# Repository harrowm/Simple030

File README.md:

# Simple030
A simple 68030 SBC heavily based on the rosco_m68k 030 board and running that board's firmware.  

The idea is to run all the glue logic from a ATF1508 and to program the logic using verilog.  

Status of 11th Feb 2025, in design - not built or tested.  The verilog does program ok onto a ATF1508.

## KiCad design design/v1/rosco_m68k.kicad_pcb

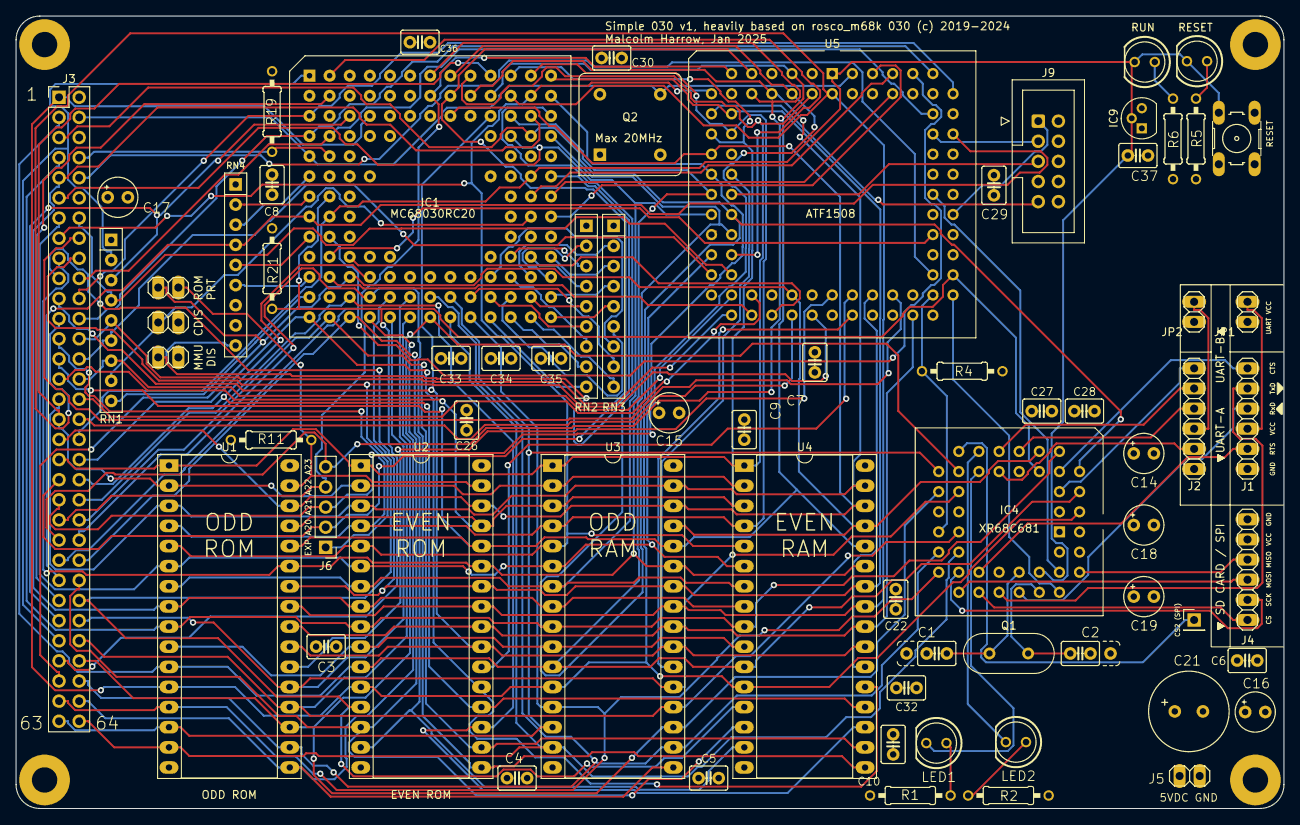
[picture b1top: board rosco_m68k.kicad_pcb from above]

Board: 4 copper layers, 160.0 x 100.0 mm, 73 parts (0 on the bottom side), 129 nets.

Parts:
C1, C2: 7pF; C2.5_or_3.5-3
C3, C4, C5, C6, C7, C8, C9, C10, C22, C26, C27, C28, C29, C30, C32, C33, C34, C35, C36: 100nF; C2.5-3
C14, C15, C16, C17, C18, C19: 100uF; E2,5-5
C21: 470uF; E3,5-10
C37: 0.01uF; C2.5-3
H1, H2, H3, H4: MountingHole; MountingHole_3.2mm_M3_Pad
IC1: MC68030RC_PGA; MC68030RC
IC4: XR68C681CJTR-F; PLCC-44_THT-Socket
IC9: DS1233-10+; TO-92
J1: UART_A; 1X06
J2: UART_B; 1X06
J3: Conn_02x32_Odd_Even; PinHeader_2x32_P2.54mm_Vertical
J4: Conn_01x06; 1X06
J5: PWR; 1X02
J6: Conn_01x05_Male; PinHeader_1x05_P2.54mm_Vertical
J7: Conn_01x01_Male; PinHeader_1x01_P2.54mm_Vertical
J9: Conn_02x05_Odd_Even; IDC-Header_2x05_P2.54mm_Vertical
JP1, JP2, JP3, JP5, JP6: Jumper; 1X02
LED1, LED6: GREEN; LED5MM
LED2, LED5: RED; LED5MM
Q1: 3.6864MHz; Crystal_HC49-4H_Vertical
Q2: 5H8ET-20.000; Oscillator_DIP-8
R1, R2: 330R; 0207_10
R4: 4K7; 0207_10
R5, R6: 1K; 0207_10
R11, R19: 10K; 0207_10
R21: 1K2; 0207_10
RN1, RN4: 4K7; R_Array_SIP9
RN2: 10K; R_Array_SIP9
RN3: R_Network08; R_Array_SIP9
SW1: SW_Push; B3F-10XX
U1, U2: SST39SF040; DIP-32_W15.24mm_Socket_LongPads
U3, U4: AS6C4008-55PCN; DIP-32_W15.24mm_Socket_LongPads
U5: ATF1508; PLCC-84_THT-Socket

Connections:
A0: IC1.A2 (A0), U5.29 (I/O)
A1: IC1.C4 (A1), IC4.2 (A1), J3.1, U1.12 (A0), U2.12 (A0), U3.12 (A0), U4.12 (A0), U5.28 (I/O)
A2: IC1.D13 (A2), IC4.4 (A2), J3.3, U1.11 (A1), U2.11 (A1), U3.11 (A1), U4.11 (A1), U5.27 (I/O)
A3: IC1.D12 (A3), IC4.6 (A3), J3.5, U1.10 (A2), U2.10 (A2), U3.10 (A2), U4.10 (A2), U5.25 (I/O)
A4: IC1.C13 (A4), IC4.7 (A4), J3.7, U1.9 (A3), U2.9 (A3), U3.9 (A3), U4.9 (A3)
A5: IC1.C12 (A5), J3.9, U1.8 (A4), U2.8 (A4), U3.8 (A4), U4.8 (A4)
A6: IC1.D11 (A6), J3.11, U1.7 (A5), U2.7 (A5), U3.7 (A5), U4.7 (A5), U5.24 (I/O)
A7: IC1.B13 (A7), J3.13, U1.6 (A6), U2.6 (A6), U3.6 (A6), U4.6 (A6), U5.20 (PD1/I/O)
A8: IC1.B12 (A8), J3.15, U1.5 (A7), U2.5 (A7), U3.5 (A7), U4.5 (A7), U5.12 (I/O)
A9: IC1.C11 (A9), J3.17, U1.27 (A8), U2.27 (A8), U3.27 (A8), U4.27 (A8), U5.22 (I/O)
A10: IC1.A13 (A10), J3.19, U1.26 (A9), U2.26 (A9), U3.26 (A9), U4.26 (A9), U5.15 (I/O)
A11: IC1.C10 (A11), J3.21, U1.23 (A10), U2.23 (A10), U3.23 (A10), U4.23 (A10), U5.21 (I/O)
A12: IC1.B11 (A12), J3.23, U1.25 (A11), U2.25 (A11), U3.25 (A11), U4.25 (A11), U5.2 (GCLK2/OE2/I)
A13: IC1.A12 (A13), J3.25, U1.4 (A12), U2.4 (A12), U3.4 (A12), U4.4 (A12), U5.17 (I/O)
A14: IC1.B10 (A14), J3.27, U1.28 (A13), U2.28 (A13), U3.28 (A13), U4.28 (A13), U5.5 (I/O)
A15: IC1.A11 (A15), J3.29, U1.29 (A14), U2.29 (A14), U3.3 (A14), U4.3 (A14), U5.16 (I/O)
A16: IC1.B9 (A16), J3.31, U1.3 (A15), U2.3 (A15), U3.31 (A15), U4.31 (A15), U5.8 (I/O)
A17: IC1.A10 (A17), J3.33, U1.2 (A16), U2.2 (A16), U3.2 (A16), U4.2 (A16)
A18: IC1.C8 (A18), J3.35, U1.30 (A17), U2.30 (A17), U3.30 (A17), U4.30 (A17), U5.18 (I/O)
A19: IC1.A9 (A19), J3.37, U1.1 (A18), U2.1 (A18), U3.1 (A18), U4.1 (A18), U5.4 (I/O)
A20: IC1.B8 (A20), J3.39, J6.2, U5.9 (I/O)
A21: IC1.A8 (A21), J3.41, J6.3, U5.6 (I/O)
A22: IC1.B7 (A22), J3.43, J6.4, U5.11 (I/O)
A23: IC1.A7 (A23), J3.45, J6.5, U5.10 (I/O)
AS: IC1.J2 (AS), J3.47, U5.77 (I/O)
BERR: IC1.H1 (BERR), J3.49, RN4.4 (R3), U5.70 (I/O)
BG: IC1.B2 (BG), J3.51
BGACK: IC1.C3 (BGACK), J3.53, RN1.3 (R2)
BR: IC1.A1 (BR), J3.55, RN1.2 (R1)
CBACK: IC1.J1 (CBACK), RN4.5 (R4)
CDIS: IC1.H12 (CDIS), JP6.1 (A), RN1.8 (R7)
CIIN: IC1.L1 (CIIN), RN4.6 (R5)
CLK: IC1.E1 (CLKIN), J3.4, Q2.5 (OUT), U5.83 (GCLK1/I)
CTSA: IC4.8 (IP0), J1.6
CTSB: IC4.5 (IP1), J2.6
D0: IC1.N9 (D16), IC4.28 (D0), J3.61, U1.13 (D0), U3.13 (DQ0)
D1: IC1.M8 (D17), IC4.18 (D1), J3.63, U1.14 (D1), U3.14 (DQ1)
D2: IC1.N8 (D18), IC4.27 (D2), J3.64, U1.15 (D2), U3.15 (DQ2)
D3: IC1.N7 (D19), IC4.19 (D3), J3.62, U1.17 (D3), U3.17 (DQ3)
D4: IC1.M7 (D20), IC4.26 (D4), J3.60, U1.18 (D4), U3.18 (DQ4)
D5: IC1.N6 (D21), IC4.20 (D5), J3.58, U1.19 (D5), U3.19 (DQ5)
D6: IC1.M6 (D22), IC4.25 (D6), J3.56, U1.20 (D6), U3.20 (DQ6)
D7: IC1.N5 (D23), IC4.21 (D7), J3.54, U1.21 (D7), U3.21 (DQ7)
D8: IC1.M5 (D24), J3.52, U2.13 (D0), U4.13 (DQ0)
D9: IC1.N4 (D25), J3.50, U2.14 (D1), U4.14 (DQ1)
D10: IC1.N3 (D26), J3.48, U2.15 (D2), U4.15 (DQ2)
D11: IC1.M4 (D27), J3.46, U2.17 (D3), U4.17 (DQ3)
D12: IC1.N2 (D28), J3.44, U2.18 (D4), U4.18 (DQ4)
D13: IC1.M3 (D29), J3.42, U2.19 (D5), U4.19 (DQ5)
D14: IC1.L4 (D30), J3.40, U2.20 (D6), U4.20 (DQ6)
D15: IC1.N1 (D31), J3.38, U2.21 (D7), U4.21 (DQ7)
DBEN: IC1.M1 (DBEN), RN1.9 (R8)
DS: IC1.K2 (DS), U5.61 (I/O)
DSACK0: IC1.F1 (DSACK0), RN4.3 (R2)
DTACK: IC1.G2 (DSACK1), IC4.10 (*DTALK), J3.57, R21.2, U5.56 (I/O)
DUAIACK: IC4.41 (*IACK), U5.65 (I/O)
DUAIRQ: IC4.24 (INTR), R4.2, U5.55 (I/O)
DUASEL: IC4.39 (CS), U5.54 (I/O)
E: J3.10, U5.57 (I/O)
EVENRAMSEL: U4.22 (CE), U5.48 (I/O)
EVENROMSEL: U2.22 (CE), U5.46 (I/O/PD2)
EXPSEL: J3.18, J6.1, U5.41 (I/O)
FC0: IC1.D2 (FC0), J3.20, U5.73 (I/O)
FC1: IC1.C1 (FC1), J3.22, U5.74 (I/O)
FC2: IC1.D1 (FC2), J3.24, U5.75 (I/O)
GND: C1.1, C2.1, C3.2, C4.2, C5.2, C6.2, C7.2, C8.2, C9.2, C10.2, C14.-, C15.-, C16.-, C17.-, C18.-, C19.-, C21.-, C22.2, C26.2, C27.2, C28.1, C29.1, C30.1, C32.2, C33.2, C34.2, C35.2, C36.2, C37.2, H1.1, H2.1, H3.1, H4.1, IC1.C5 (GND), IC1.C7 (GND), IC1.C9 (GND), IC1.E3 (GND), IC1.E11 (GND), IC1.F3 (GND), IC1.G3 (GND), IC1.G11 (GND), IC1.J3 (GND), IC1.J11 (GND), IC1.L5 (GND), IC1.L7 (GND), IC1.L8 (GND), IC1.L9 (GND), IC4.3 (IP3), IC4.22 (GND), IC4.42 (IP5), IC4.43 (IP4), IC9.1 (GND), J1.1, J2.1, J3.6, J4.6, J5.2, J9.2, J9.10, JP5.2 (B), JP6.2 (B), Q2.4 (GND), R6.2, RN2.1 (common), RN3.1 (common), SW1.1, U1.16 (GND), U2.16 (GND), U3.16 (VSS), U4.16 (VSS), U5.7 (GND), U5.19 (GND), U5.32 (GND), U5.42 (GND), U5.47 (GND), U5.59 (GND), U5.72 (GND), U5.82 (GND)
HALT: C37.1, IC1.F12 (RESET), IC1.H2 (HLT), IC4.38 (*RESET), IC9.2 (~RST), J3.36, LED5.K (C), LED6.K (C), SW1.2, U5.1 (GCLR/I)
IOSEL: J3.16, U5.50 (I/O)
IPL0: IC1.H13 (IPL0), U5.81 (GCLK3/I/O)
IPL1: IC1.G13 (IPL1), U5.80 (I/O)
IPL2: IC1.G12 (IPL2), U5.79 (I/O)
IRQ2: J3.28, RN1.6 (R5), U5.30 (I/O)
IRQ3: J3.14, RN1.4 (R3), U5.31 (I/O)
IRQ5: J3.26, RN1.5 (R4), U5.33 (I/O)
IRQ6: J3.30, RN1.7 (R6), U5.34 (I/O)
LDS: J3.32, U5.36 (I/O)
MMUDIS: IC1.F13 (MMUDIS), JP5.1 (A), RN4.9 (R8)
unnamed: IC4.15 (OP3), LED2.K (C)
unnamed: IC4.16 (OP5), LED1.K (C)
unnamed: C1.2, IC4.36 (X1/CLK), Q1.1
unnamed: C2.2, IC4.37 (X2), Q1.2
unnamed: LED1.A, R1.1
unnamed: LED2.A, R2.1
unnamed: LED5.A, R5.1
unnamed: LED6.A, R6.1
ODDRAMSEL: U3.22 (CE), U5.45 (I/O)
ODDROMSEL: U1.22 (CE), U5.44 (I/O)
ROM_RW: JP3.2 (B), R11.2, U1.31 (PGM), U2.31 (PGM)
RTSA: IC4.32 (OP0), J1.2
RTSB: IC4.14 (OP1), J2.2
RW: IC1.L3 (R_W), IC4.9 (*R/*W), J3.59, JP3.1 (A), U3.29 (WE), U4.29 (WE), U5.40 (I/O)
RXDA: IC4.35 (RXDA), J1.4
RXDB: IC4.11 (RXDB), J2.4
SIZ0: IC1.L2 (SIZ0), U5.35 (I/O)
SIZ1: IC1.K3 (SIZ1), U5.37 (I/O)
SPICLK: IC4.30 (OP4), J4.2
SPICS: IC4.31 (OP2), J4.1
SPICS2: IC4.17 (OP7), J7.1
SPIMISO: IC4.40 (IP2), J4.4
SPIMOSI: IC4.29 (OP6), J4.3
STERM: IC1.G1 (STERM), RN4.2 (R1)
TCK: J9.1, U5.62 (TCK/I/O)
TDI: J9.9, U5.14 (TDI/I/O)
TDO: J9.3, U5.71 (TDO/I/O)
TMS: J9.5, U5.23 (TMS/I/O)
TXDA: IC4.33 (TXDA), J1.5
TXDB: IC4.13 (TXDB), J2.5
UD0: IC1.K13 (D0), RN3.3 (R2)
UD1: IC1.K12 (D1), RN2.4 (R3)
UD2: IC1.L13 (D2), RN2.2 (R1)
UD3: IC1.M13 (D3), RN3.4 (R3)
UD4: IC1.L12 (D4), RN3.2 (R1)
UD5: IC1.K11 (D5), RN2.3 (R2)
UD6: IC1.M12 (D6), RN2.5 (R4)
UD7: IC1.L11 (D7), RN2.7 (R6)
UD8: IC1.N13 (D8), RN3.5 (R4)
UD9: IC1.M11 (D9), RN3.6 (R5)
UD10: IC1.L10 (D10), RN3.7 (R6)
UD11: IC1.N12 (D11), RN3.9 (R8)
UD12: IC1.M10 (D12), RN2.6 (R5)
UD13: IC1.N11 (D13), RN2.8 (R7)
UD14: IC1.M9 (D14), RN3.8 (R7)
UD15: IC1.N10 (D15), RN2.9 (R8)
UDS: J3.34, U5.39 (I/O)
VCC: C3.1, C4.1, C5.1, C6.1, C7.1, C8.1, C9.1, C10.1, C14.+, C15.+, C16.+, C17.+, C18.+, C19.+, C21.+, C22.1, C26.1, C27.1, C28.2, C29.2, C30.2, C32.1, C33.1, C34.1, C35.1, C36.1, IC1.C6 (VCC), IC1.D4 (VCC), IC1.D10 (VCC), IC1.F2 (VCC), IC1.F11 (VCC), IC1.H3 (VCC), IC1.H11 (VCC), IC1.K4 (VCC), IC1.K10 (VCC), IC1.L6 (VCC), IC4.44 (VCC), IC9.3 (VCC), J3.2, J4.5, J5.1, JP1.2 (B), JP2.2 (B), Q2.8 (Vcc), R1.2, R2.2, R4.1, R5.2, R11.1, R19.1, R21.1, RN1.1 (common), RN4.1 (common), U1.32 (VCC), U2.32 (VCC), U3.32 (VCC), U4.32 (VCC), U5.3 (VCCINT), U5.13 (VCCIO), U5.26 (VCCIO), U5.38 (VCCIO), U5.43 (VCCINT), U5.53 (VCCIO), U5.66 (VCCIO), U5.78 (VCCIO)
VCCUA: J1.3, JP1.1 (A)
VCCUB: J2.3, JP2.1 (A)
VPA: IC1.E2 (AVEC), J3.8, R19.2
WR: U1.24 (OE), U2.24 (OE), U3.24 (OE), U4.24 (OE), U5.51 (I/O)

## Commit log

2025-01-27 Tidy of files
2025-01-27 Start on verilog
2025-01-28 Start verilog pin mapping
2025-01-29 Initial pin fit
2025-01-30 Move ATF1508 VCCIO Cap and correct IRQ code
2025-02-01 Verilog written except for generation of E
2025-02-02 Further progress on verilog
2025-02-04 Fixed E signal by renaming to ESIG
2025-02-06 First program of the ATF1508
2025-02-06 Add DS1233
2025-02-11 Tidy up readme
2025-02-12 Tidy up board 3D image

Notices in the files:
design/v1/rosco_m68k.kicad_pcb:
Open Source Hardware licenced under CERN Open Hardware Licence
Copyright ©2019-2024 Ross Bamford & Contributors
Simple 030 v1, heavily based on rosco_m68k 030 (c) 2019-2024
